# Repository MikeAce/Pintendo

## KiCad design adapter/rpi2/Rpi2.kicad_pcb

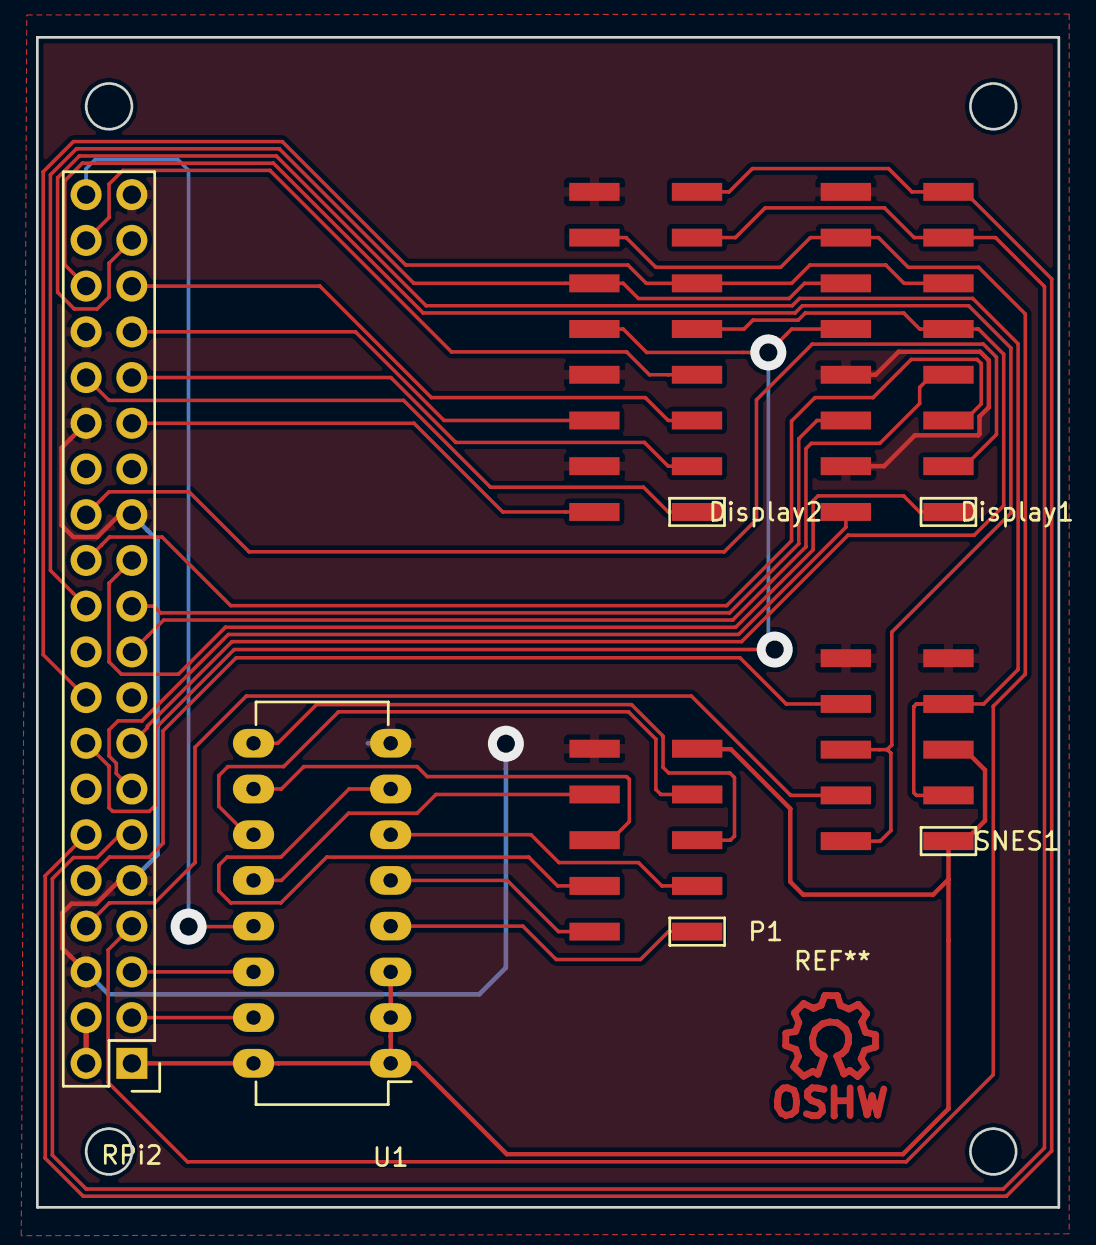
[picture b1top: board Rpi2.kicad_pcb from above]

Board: 2 copper layers, 56.8 x 65.0 mm, 6 parts (0 on the bottom side), 37 nets.

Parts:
Display1, Display2: CONN_02X08; Pin_Header_SMD_02x08
P1: CONN_02X05; Pin_Header_SMD_02x05
RPi2: CONN_02X20; Pin_Header_Straight_2x20
SNES1: CONN_02X05; Pin_Header_SMD_02x05
U1: PCF8574; DIP-16_W7.62mm_LongPads

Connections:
3V3: P1.9, RPi2.1, SNES1.1, SNES1.5, U1.1, U1.2, U1.3, U1.16
5V: RPi2.2, RPi2.4
/OE: Display1.15, Display2.15, RPi2.12
A: Display1.9, Display2.9, RPi2.15
B: Display1.10, Display2.10, RPi2.16
C: Display1.11, Display2.11, RPi2.18
CLK: Display1.13, Display2.13, RPi2.11
D: Display1.12, Display2.12, RPi2.22
GND: Display1.4, Display1.8, Display1.16, Display2.4, Display2.8, Display2.16, P1.10, RPi2.6, RPi2.9, RPi2.25, RPi2.30, RPi2.34, RPi2.39, SNES1.9, SNES1.10, U1.8
unnamed: P1.1, U1.4
unnamed: P1.2, U1.5
unnamed: P1.3, U1.6
unnamed: P1.4, U1.7
unnamed: P1.5, U1.9
unnamed: P1.6, U1.10
unnamed: P1.7, U1.11
unnamed: P1.8, U1.12
unnamed: RPi2.3, U1.15
unnamed: RPi2.5, U1.14
unnamed: RPi2.40, U1.13
SNES_CLK: RPi2.36, SNES1.2, SNES1.6
SNES_DATA0: RPi2.8, SNES1.4
SNES_DATA1: RPi2.10, SNES1.8
SNES_LATCH: RPi2.37, SNES1.3, SNES1.7
STB: Display1.14, Display2.14, RPi2.7
[1]B0: Display1.3, RPi2.26
[1]B1: Display1.7, RPi2.19
[1]G0: Display1.2, RPi2.13
[1]G1: Display1.6, RPi2.21
[1]R0: Display1.1, RPi2.23
[1]R1: Display1.5, RPi2.24
[2]B0: Display2.3, RPi2.31
[2]B1: Display2.7, RPi2.38
[2]G0: Display2.2, RPi2.29
[2]G1: Display2.6, RPi2.33
[2]R0: Display2.1, RPi2.32
[2]R1: Display2.5, RPi2.35

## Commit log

2015-10-04 Inital
    support RGBMatrix
    support SNESController
    small example program
2015-10-04 Revert "Inital"
    This reverts commit 1b20ea70eadca16c529dcba12933e88b540177a9.
2015-10-04 Initial Branch
    - support RGBMatrix and SNESController
    - simple Demoprogram
2015-10-04 BugFix + lcdDisplay
2015-10-09 add adapter board for RaspberryPi2 (unfinished)
2015-10-17 routing all traces on pcb
2015-10-18 adding PCF8574, finished routing, drill holes unsuitable
2015-10-23 finalized board
2016-01-15 changed part names
2016-02-04 adding making of document
2016-02-18 BugFix + Add NetBeans Project
2016-03-30 Changed Animation
2016-06-20 add Datasheets
2016-06-20 rename file
2016-07-09 add schematic of Audio board
2017-09-30 Makefile: - rename pitendo -> pintendo - add missing object filed
    SNESController.c:
    - stopPollButtons in snesClose()
    - cleanup tabs
    bcm2835.h:
    - upgrade version 1.42 -> 1.49
    main.c:
2017-10-02 NetBeans Projekt angepasst. Da dies ein 1-Mann Projekt ist, habe ich auch nbproject/private/ unter Versionskontrolle gestellt.
2017-10-04 Makefile erweitert (clean + proper) main.c: printf debugging für die SNES buttons
2017-10-09 add some schematics, rename some files
2018-01-12 finally got the snes pads working now we can rewrite/complete the snes interface
2018-06-21 integrate code in a Clode::Blocks project
2018-06-21 remove netbeans project
2018-06-21 rename LCDDisplay -> LCDisplay
2018-06-21 rename LCDDisplay -> LCDisplay (project file)
